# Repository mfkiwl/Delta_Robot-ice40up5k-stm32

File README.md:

[//]: # (Programado con lenguaje Markdown)

# DELTA ROBOT

Diseño robot delta

## Introducción

## Requerimientos

## Diseño

Se creo un [foro](https://xmartplm.com/covid19-colombia/) para la discusión en comunidad sobre el diseño de un ventilador para afrontar la crisis del COVID-19. Como conclusión se deben afrontar los siguientes temas:

* Seleccionar tipo de control.
* Diseño mecánico.
* Diseño electrónico.
* Realización prototipo.
* Pruebas.

### Diseño electrónico general

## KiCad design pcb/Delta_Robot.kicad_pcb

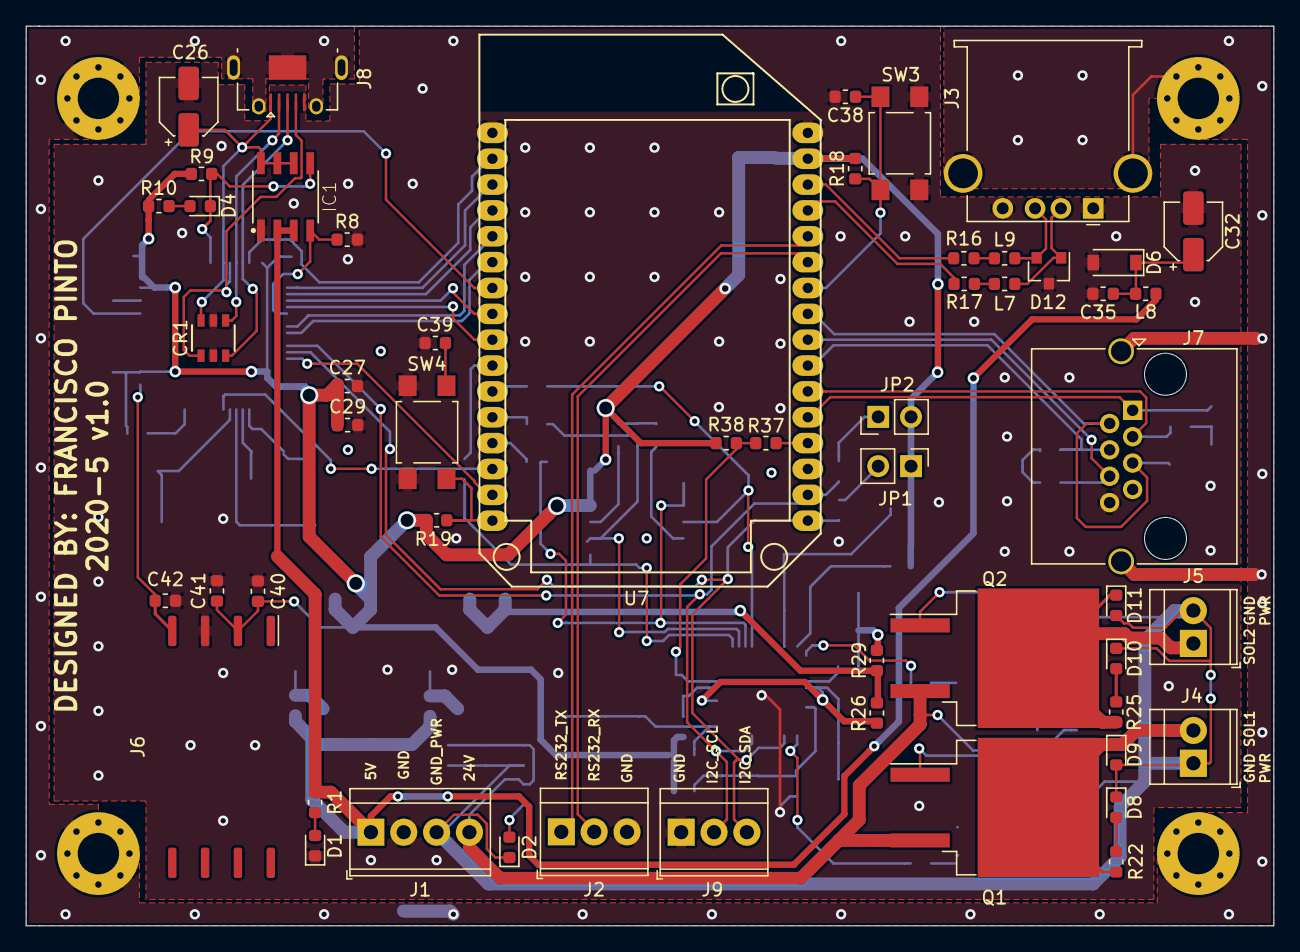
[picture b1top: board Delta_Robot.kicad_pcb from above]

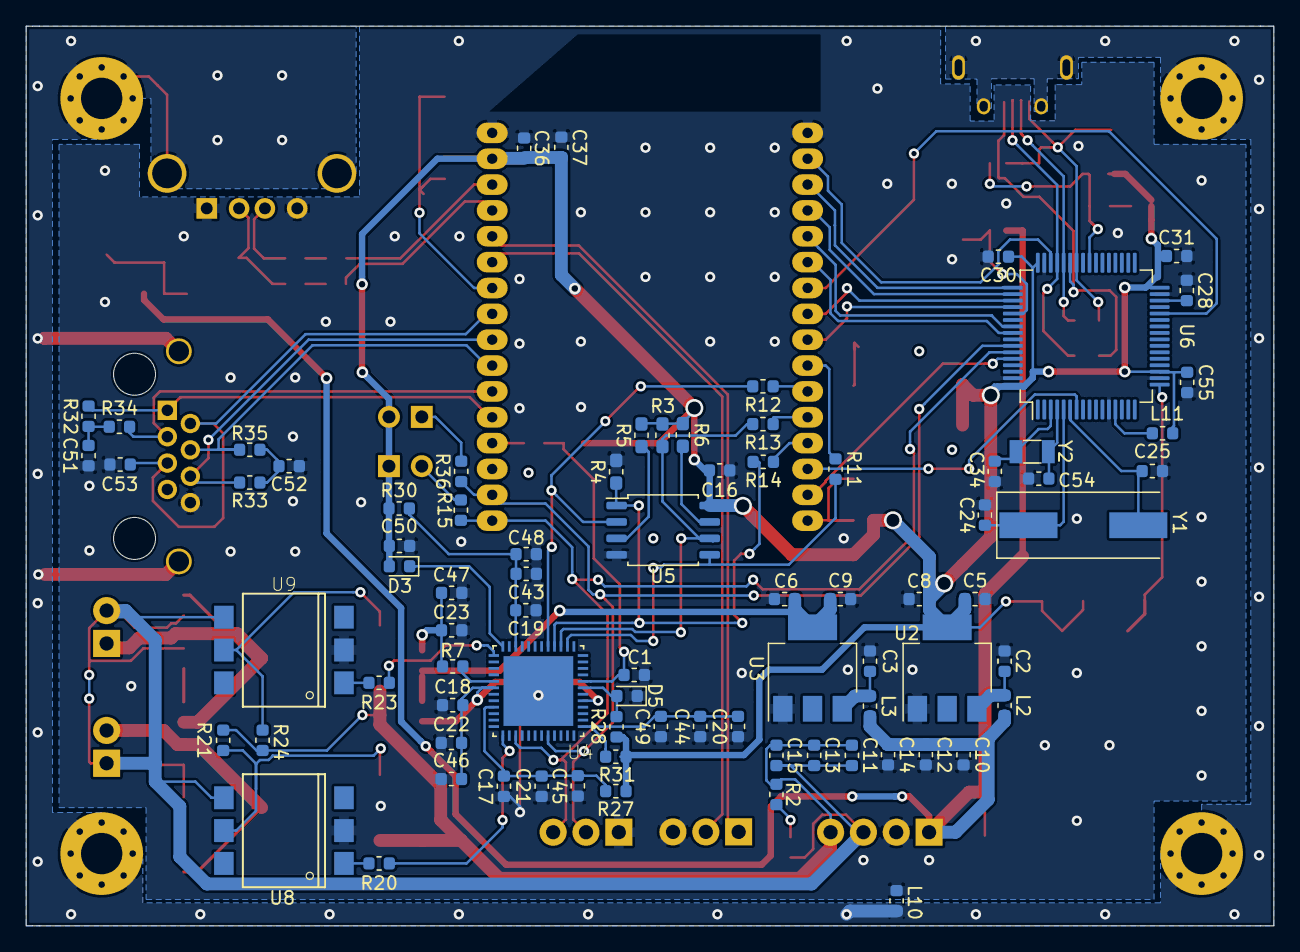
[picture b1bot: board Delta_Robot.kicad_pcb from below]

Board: 2 copper layers, 96.5 x 69.6 mm, 139 parts (81 on the bottom side), 87 nets.

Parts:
C1, C5, C6, C12, C13, C16, C21, C22, C27, C29, C30, C31, C36, C37, C43, C44, C50, C55: 0.1uF; C_0603_1608Metric
C2, C17, C18, C19, C20, C40, C53: 1uF; C_0603_1608Metric
C3, C9: 33uF; C_0603_1608Metric
C8: 4.7uF; C_0603_1608Metric
C10, C11: 220uF; C_0603_1608Metric
C14, C15: 1nF; C_0603_1608Metric
C23: 10uF; C_0603_1608Metric
C24, C25: 4.3pF; C_0603_1608Metric
C26: 4.7uF; CP_Elec_4x3
C28: 2.2uF; C_0603_1608Metric
C32: 22uF; CP_Elec_4x3
C34, C54: 2pF; C_0603_1608Metric
C35, C38, C39: 0.1u; C_0603_1608Metric
C41, C45, C46, C48, C49: 10nF; C_0603_1608Metric
C42: 470pF; C_0603_1608Metric
C47, C51, C52: 100nF; C_0603_1608Metric
CR1: ESDA6V1BC6
D1, D2, D4, D5, D8, D10: LED; LED_0603_1608Metric
D3, D9, D11: CDBU0520; D_0603_1608Metric
D6: 1N4733AW; D_SOD-123
D12: NUP2105L; SOT-23
H1, H2, H3, H4: MountingHole_Pad; MountingHole_3.2mm_M3_Pad_Via
IC1: STMPS2151MTR; SOIC127P600X175-8N
J1: Conn_01x04; TerminalBlock_TE_282834-4_1x04_P2.54mm_Horizontal
J2, J9: Conn_01x03; TerminalBlock_TE_282834-3_1x03_P2.54mm_Horizontal
J3: USB_A; USB_A_Stewart_SS-52100-001_Horizontal
J4, J5: Conn_01x02; TerminalBlock_TE_282834-2_1x02_P2.54mm_Horizontal
J6: MP3V5050VC6U
J7: RJ45; RJ45_Amphenol_RJHSE5380
J8: USB_OTG; USB_Micro-AB_Molex_47590-0001
JP1, JP2: Jumper; PinHeader_1x02_P2.54mm_Vertical
L2, L3: BLM18SG121TN1D; L_0603_1608Metric
L7, L9, L11: SRF2012-900YA; L_0603_1608Metric
L8, L10: 742792651; L_0603_1608Metric
Q1, Q2: IRF9540STRLPBF; TO-263-2
R1: 2k; R_0603_1608Metric
R2: 4k7; R_0603_1608Metric
R3, R5, R6: 10k; R_0603_1608Metric_Pad1.05x0.95mm_HandSolder
R4: 10K; R_0603_1608Metric_Pad1.05x0.95mm_HandSolder
R7, R11, R12, R13, R14, R37: 100; R_0603_1608Metric
R8, R9, R18, R19, R38: 10k; R_0603_1608Metric
R10: 620; R_0603_1608Metric
R15, R36: 4.7k; R_0603_1608Metric
R16, R17: 0K; R_0603_1608Metric
R20, R23: 330; R_0603_1608Metric
R21, R24: 100k; R_0603_1608Metric
R22, R25: 1k; R_0603_1608Metric
R26, R27, R29, R30, R31: 1; R_0603_1608Metric
R28: 2.2k; R_0603_1608Metric
R32, R33, R34, R35: 50; R_0603_1608Metric
SW3, SW4: TL3305A; SW_SPST_TL3305A
U2: LDL1117S33R; SOT-223-3_TabPin2
U3: ZLDO1117G12TA; SOT-223-3_TabPin2
U4: ICE40UP5K-SG48I; QFN50P700X700X100-49N
U5: W25Q64JVSSIQ; SOIC-8_5.23x5.23mm_P1.27mm
U6: STM32F412RGT6; LQFP-64_10x10mm_P0.5mm
U7: Omega2+; ONION_OMEGA2
U8, U9: 4N25-X007T; DIL6-SMD
Y1: 8MHz; Crystal_SMD_HC49-SD
Y2: 32.768KHZ; Crystal_SMD_3215-2Pin_3.2x1.5mm

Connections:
+1V2_FPGA: C6.1, C9.1, R26.2, R29.2, U3.2
+3V3: C5.1, C8.1, C16.1, C27.1, C29.1, C30.1, C31.1, C36.1, C37.1, C40.1, C41.1, C50.1, C55.1, D3.2, J6.2, JP1.1, JP2.2, L11.1, R3.1, R5.1, R6.1, R9.2, R10.2, R18.1, R19.1, R27.2, R28.2, R30.2, R31.2, R38.1, U2.2, U5.8, U6.19, U6.32, U6.48, U6.64, U7.31
+5V: C10.1, C12.1, C14.1, IC1.2, IC1.3, J1.1, L2.2, L3.2, L8.1, R1.1
+24V: C11.2, C13.2, C15.2, J1.4, Q1.3, Q2.3, R2.1, R21.1, R24.1
/External Communications/EXT_I2C0: J9.2, R36.2, U4.44, U6.58, U7.18
/External Communications/EXT_I2C1: J9.3, R15.2, U4.39, U6.59, U7.17
/External Communications/EXT_RS232_RX: J2.2, U7.27
/External Communications/EXT_RS232_TX: J2.1, U7.28
/FPGA/FPGA_CDONE: D5.2, R28.1, U4.7
/FPGA/FPGA_SOLENOID1: R20.2, U4.37
/FPGA/FPGA_SOLENOID2: R23.2, U4.25
/FPGA/FPGA_SPI0: R11.2, U4.14, U5.5
/FPGA/FPGA_SPI1: R12.2, U4.17, U5.2
/FPGA/FPGA_SPI2: R3.2, R13.2, U4.15, U5.6
/FPGA/FPGA_SPI3: R4.1, R14.2, U4.16, U5.1
/FPGA/FPGA_SPI_VCCIO_1: C19.2, C43.2, C48.2, R30.1, U4.22
/FPGA/FPGA_VCC: C18.2, C22.2, C46.2, R26.1, U4.5, U4.30
/FPGA/FPGA_VCCIO_2: C20.2, C44.2, C49.2, R31.1, U4.1
/FPGA/FPGA_VCCIO_O: C17.2, C21.2, C45.2, R27.1, U4.33
/FPGA/FPGA_VCCPLL: R7.1, U4.29
/FPGA/FPGA_VPP_2V5: D3.1, U4.24
/FPGA/~FPGA_CRESET_B: C1.2, R37.2, R38.2, U4.8
/FPGA/~FPGA_RESET: R37.1, U7.20
/Onion Omega 2/ETH_PWR: C53.1, J7.2, J7.5, U7.25
/Onion Omega 2/OMEGA2_ETH_RX+: J7.1, R32.2, U7.21
/Onion Omega 2/OMEGA2_ETH_RX-: J7.3, R34.2, U7.22
/Onion Omega 2/OMEGA2_ETH_TX+: J7.4, R35.1, U7.23
/Onion Omega 2/OMEGA2_ETH_TX-: J7.6, R33.1, U7.24
/Onion Omega 2/OMEGA2_FW_RST: C38.1, R18.2, SW3.2, U7.26
/Onion Omega 2/OMEGA2_JTAG_TCK: U6.49, U7.3
/Onion Omega 2/OMEGA2_JTAG_TDI: U6.50, U7.4
/Onion Omega 2/OMEGA2_JTAG_TDO: U6.55, U7.5
/Onion Omega 2/OMEGA2_JTAG_TMS: U6.46, U7.2
/Onion Omega 2/OMEGA2_JTAG_TRST: U6.56, U7.6
/Onion Omega 2/OMEGA2_USB_D+: R16.1, U7.30
/Onion Omega 2/OMEGA2_USB_D-: R17.2, U7.29
/Onion Omega 2/Omega2_SER1_RX: U6.51, U7.8
/Onion Omega 2/Omega2_SER1_TX: U6.52, U7.9
/Onion Omega 2/STM32_BOOT0: U6.60, U7.15
/Onion Omega 2/STM32_BOOT1: U6.28, U7.7
/Onion Omega 2/STM32_NRST: U6.7, U7.14
/Onion Omega 2/~OMEGA2_RST: C39.1, R19.2, SW4.2, U7.16
/STM32/PRESSURE_AIN: C42.1, J6.4, U6.17
/STM32/STM32_USB_DM: CR1.4, J8.2, U6.44
/STM32/STM32_USB_DP: CR1.3, J8.3, U6.45
/STM32/STM32_USB_ID: CR1.1, J8.4, U6.43
/STM32/STM32_USB_OverCurrent: D4.1, IC1.5, R9.1, U6.40
/STM32/STM32_USB_PowerSwitchOn: IC1.4, R8.2, U6.53
/STM32/STM32_USB_VBUS: C26.1, CR1.6, IC1.6, IC1.7, IC1.8, J8.1, U6.42
GND: C1.1, C2.2, C3.2, C5.2, C6.2, C8.2, C9.2, C10.2, C12.2, C14.2, C16.2, C17.1, C18.1, C19.1, C20.1, C21.1, C22.1, C23.1, C24.2, C25.2, C26.2, C27.2, C28.2, C29.2, C30.2, C31.2, C32.2, C34.2, C35.2, C36.2, C37.2, C38.2, C39.2, C40.2, C41.2, C42.2, C43.1, C44.1, C45.1, C46.1, C47.1, C48.1, C49.1, C50.2, C51.1, C52.2, C53.2, C54.2, C55.2, CR1.2, CR1.5, D1.1, D5.1, D6.2, D12.3, IC1.1, J1.2, J2.3, J3.1, J3.4, J6.3, J7.8, J8.5, J9.1, L10.2, R4.2, R8.1, SW3.1, SW4.1, U2.1, U3.1, U4.EP, U5.4, U6.12, U6.18, U6.31, U6.47, U6.63, U7.1, U7.32, U8.2, U9.2
GNDPWR: C11.1, C13.1, C15.1, D2.1, D8.1, D9.2, D10.1, D11.2, J1.3, J4.1, J5.2, U8.4, U9.4
GND_CASE: H1.1, H2.1, H3.1, H4.1, J3.5, J7.SH, J8.6, L10.1
unnamed: C2.1, L2.1, U2.3
unnamed: C3.1, L3.1, U3.3
unnamed: C23.2, C47.2, R7.2, R29.1
unnamed: C24.1, U6.5, Y1.1
unnamed: C25.1, U6.6, Y1.2
unnamed: C28.1, U6.30
unnamed: C32.1, C35.1, D6.1, L8.2
unnamed: C34.1, U6.3, Y2.1
unnamed: C51.2, R32.1, R34.1
unnamed: C52.1, R33.2, R35.2
unnamed: C54.1, U6.4, Y2.2
unnamed: D1.2, R1.2
unnamed: D2.2, R2.2
unnamed: D4.2, R10.1
unnamed: D8.2, R22.2
unnamed: D9.1, J4.2, Q1.2, R22.1
unnamed: D10.2, R25.2
unnamed: D11.1, J5.1, Q2.2, R25.1
unnamed: D12.1, J3.2, L7.2
unnamed: D12.2, J3.3, L9.2
unnamed: JP1.2, R15.1
unnamed: JP2.1, R36.1
unnamed: L7.1, R17.1
unnamed: L9.1, R16.2
unnamed: L11.2, U6.13
unnamed: Q1.1, R21.2, U8.5
unnamed: Q2.1, R24.2, U9.5
unnamed: R5.2, U5.3
unnamed: R6.2, U5.7
unnamed: R11.1, U7.10
unnamed: R12.1, U7.11
unnamed: R13.1, U7.12
unnamed: R14.1, U7.13
unnamed: R20.1, U8.1
unnamed: R23.1, U9.1

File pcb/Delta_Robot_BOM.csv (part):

Reference, Quantity, Value, Footprint, Datasheet, Digikey, MPN, Mouser, Breakout board, Field4, Field5, Field6, Value2, Description, Manufacturer_Name, Drawing
C10 C3 C9 ,3,"22uF","Capacitor_SMD:C_0603_1608Metric","~","1276-2868-1-ND","CL10A226MQ8NRNE","","","","","","","","",""
C11 C23 ,2,"10uF","Capacitor_SMD:C_0603_1608Metric","~","1253-CM105X5R106M25ATCT-ND","CM105X5R106M25AT","346-CM105X5R106M25AT","","","","","","","",""
C12 C13 C5 C6 C16 C22 C47 C50 C21 C43 C44 C1 C55 C29 C30 C31 C27 C36 C35 C38 C39 C52 C37 ,23,"0.1uF","Capacitor_SMD:C_0603_1608Metric","~","399-7845-1-ND","C0603C104M5RACTU","80-C0603C104M5R","","","","","","","",""
C14 C15 ,2,"1nF","Capacitor_SMD:C_0603_1608Metric","~","311-1080-1-ND","CC0603KRX7R9BB102","603-CC603KRX7R9BB102","","","","","","","",""
C2 C18 C17 C19 C20 C53 C40 ,7,"1uF","Capacitor_SMD:C_0603_1608Metric","~","1276-1102-1-ND","CL10A105KA8NNNC","","","","","","","","",""
C25 C24 ,2,"4.3pF","Capacitor_SMD:C_0603_1608Metric","~","1276-2309-1-ND","CL10C4R3CB8NNNC","","","","","","","","",""
C26 ,1,"4.7uF","Capacitor_SMD:CP_Elec_4x3","https://www.we-online.de/katalog/datasheet/865060240001.pdf","732-8569-1-ND","865060240001","710-865060240001","","","","","","","",""
C28 ,1,"2.2uF","Capacitor_SMD:C_0603_1608Metric","~","587-1430-1-ND","EMK107BJ225KA-T","963-EMK107BJ225KA-T","","","","","","","",""
C32 ,1,"22uF","Capacitor_SMD:CP_Elec_4x3","https://www.we-online.de/katalog/datasheet/865060240001.pdf","732-8569-1-ND","865060240001","710-865060240001","","","","","","","",""
C42 ,1,"470pF","Capacitor_SMD:C_0603_1608Metric","~","399-1075-1-ND","C0603C471K5RACTU","80-C0603C471K5R","","","","","","","",""
C46 C45 C48 C49 C41 ,5,"10nF","Capacitor_SMD:C_0603_1608Metric","~","399-7842-1-ND","C0603C103M5RACTU","80-C0603C103M5R","","","","","","","",""
C51 ,1,"100nF","Capacitor_SMD:C_0603_1608Metric","~","399-1100-1-ND","C0603C104Z3VACTU","80-C0603C104Z3V","","","","","","","",""
C54 C34 ,2,"2pF","Capacitor_SMD:C_0603_1608Metric","~","1276-2124-1-ND","CL10C020CB8NNNC","","","","","","","","",""
C8 ,1,"4.7uF","Capacitor_SMD:C_0603_1608Metric","~","1276-1907-1-ND","CL10A475MQ8NNNC","","","","","","","","",""
CR1 ,1,"ESDA6V1BC6","SMD:ESDA6V1BC6","https://www.st.com/content/ccc/resource/technical/document/d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","497-6635-1-ND","ESDA6V1BC6","511-ESDA6V1BC6","","","","","","","",""
D1 D2 D5 D4 D8 D10 ,6,"LED","LED_SMD:LED_0603_1608Metric","~","732-4971-1-ND","150060GS75000","710-150060GS75000","","","","","","","",""
D12 ,1,"NUP2105L","Package_TO_SOT_SMD:SOT-23","http://www.onsemi.com/pub_link/Collateral/NUP2105L-D.PDF","SZNUP2105LT1GOSCT-ND","SZNUP2105LT1G","863-SZNUP2105LT1G","","","","","","","",""
D3 D9 D11 ,3,"CDBU0520","Diode_SMD:D_0603_1608Metric","http://www.comchiptech.com/admin/files/product/CDBU0520-HF-R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","641-1332-1-ND","CDBU0520","750-CDBU0520","","","","","","","",""
D6 ,1,"BZT52-B5V1J","Diode_SMD:D_SOD-123","~","1727-7742-1-ND","BZT52-B5V1J","771-BZT52-B5V1J","","","","","","","",""
H1 H2 H3 H4 ,4,"MountingHole_Pad","MountingHole:MountingHole_3.2mm_M3_Pad_Via","~"
IC1 ,1,"STMPS2151MTR","SMD:SOIC127P600X175-8N","http://docs-emea.rs-online.com/webdocs/140d/0900766b8140da90.pdf","497-8349-1-ND","STMPS2151MTR","511-STMPS2151MTR","","","","","","STMICROELECTRONICS - STMPS2151MTR","STMicroelectronics",""
J1 ,1,"Conn_01x04","TerminalBlock_TE-Connectivity:TerminalBlock_TE_282834-4_1x04_P2.54mm_Horizontal","~","A98335-ND","282834-4","571-282834-4","","","","","","","",""
J2 J9 ,2,"Conn_01x03","TerminalBlock_TE-Connectivity:TerminalBlock_TE_282834-3_1x03_P2.54mm_Horizontal","~","A98334-ND","282834-3","571-2828343","","","","","","","",""
J3 ,1,"USB_A","Connector_USB:USB_A_Stewart_SS-52100-001_Horizontal","https://belfuse.com/resources/datasheets/stewartconnector/ds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","380-1412-ND","SS-52100-001","530-SS-52100-001","","","","","","","",""
J4 J5 ,2,"Conn_01x02","TerminalBlock_TE-Connectivity:TerminalBlock_TE_282834-2_1x02_P2.54mm_Horizontal","~","A98333-ND","282834-2","571-282834-2","","","","","","","",""
J6 ,1,"MP3V5050VC6U","SMD:MP3V5050VC6U","https://www.nxp.com/docs/en/data-sheet/MP3V5050V.pdf","568-MP3V5050VC6U-ND","MP3V5050VC6U","841-MP3V5050VC6U","","","","","","","",""
J7 ,1,"RJ45","Connector_RJ:RJ45_Amphenol_RJHSE5380","https://cdn.amphenol-icc.com/media/wysiwyg/files/drawing/rjh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","RJHSE-5380-ND","RJHSE-5380","523-RJHSE-5380","","","","","","","",""
J8 ,1,"USB_OTG","SMD:USB_Micro-AB_Molex_47590-0001","https://www.molex.com/pdm_docs/sd/475900001_sd.pdf","WM17144CT-ND","0475900001","538-47590-0001","","","","","","","",""
JP2 JP1 ,2,"Jumper","Connector_PinHeader_2.54mm:PinHeader_1x02_P2.54mm_Vertical","~"
L10 L8 ,2,"742792651","Inductor_SMD:L_0603_1608Metric","https://www.we-online.de/katalog/datasheet/742792651.pdf","732-1593-1-ND","742792651","710-742792651","","","","","","","",""
L11 L9 L7 ,3,"SRF2012-900YA","Inductor_SMD:L_0603_1608Metric","https://www.bourns.com/docs/Product-Datasheets/SRF2012A.pdf","SRF2012-900YACT-ND","SRF2012-900YA","652-SRF2012-900YA","","","","","","","",""
L2 L3 ,2,"BLM18SG121TN1D","Inductor_SMD:L_0603_1608Metric","~","490-3996-6-ND","BLM18SG121TN1D","81-BLM18SG121TN1D","","","","","","","",""
Q1 Q2 ,2,"IRF9540STRLPBF","Package_TO_SOT_SMD:TO-263-2","http://www.vishay.com/docs/91079/91079.pdf","IRF9540STRLPBFCT-ND","IRF9540STRLPBF","844-IRF9540STRLPBF","","","","","","","",""
R1 R7 R37 R11 R12 R13 R14 ,7,"100","Resistor_SMD:R_0603_1608Metric","~","311-100HRCT-ND","RC0603FR-07100RL","603-RC0603FR-07100RL","","","","","","","",""
R15 R36 ,2,"4.7k","Resistor_SMD:R_0603_1608Metric","~","RR08P4.7KDCT-ND","RR0816P-472-D","","","","","","","","",""
R17 R16 ,2,"0K","Resistor_SMD:R_0603_1608Metric","~","311-0.0GRCT-ND","RC0603JR-070RL","603-RC0603JR-070RL","","","","","","","",""
R2 R22 R25 ,3,"1.5k","Resistor_SMD:R_0603_1608Metric","~","A130092CT-ND","CRGCQ0603J1K5","279-CRGCQ0603J1K5","","","","","","","",""
R20 R23 ,2,"47","Resistor_SMD:R_0603_1608Metric","~","A130083CT-ND","CRGCQ0603J47R","279-CRGCQ0603J47R","","","","","","","",""
R21 R24 ,2,"100k","Resistor_SMD:R_0603_1608Metric","~","RR08P100KDCT-ND","RR0816P-104-D","754-RR0816P-104D","","","","","","","",""
R26 R29 R27 R30 R31 ,5,"1","Resistor_SMD:R_0603_1608Metric","~","311-1.00HRCT-ND","RC0603FR-071RL","603-RC0603FR-071RL","","","","","","","",""
R28 R10 ,2,"4.7","Resistor_SMD:R_0603_1608Metric","~","2019-RK73B1JTTD4R7JCT-ND","RK73B1JTTD4R7J","660-RK73B1JTTD4R7J","","","","","","","",""
R32 R34 R35 R33 ,4,"50","Resistor_SMD:R_0603_1608Metric","~","A130083CT-ND","CRGCQ0603J47R","279-CRGCQ0603J47R","","","","","","","",""
R38 R8 R9 R18 R19 ,5,"10k","Resistor_SMD:R_0603_1608Metric","~","311-10KGRCT-ND","RC0603JR-0710KL","603-RC0603JR-0710KL","","","","","","","",""
R4 R5 R6 R3 ,4,"10k","Resistor_SMD:R_0603_1608Metric_Pad1.05x0.95mm_HandSolder","~","311-10KGRCT-ND","RC0603JR-0710KL","603-RC0603JR-0710KL","","","","","","","",""
SW3 SW4 ,2,"TL3305A","Button_Switch_SMD:SW_SPST_TL3305A","https://sten-eswitch-13110800-production.s3.amazonaws.com/sy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","EG5353CT-ND","TL3305AF260QG","612-TL3305AF260QG","","","","","","","","http://spec_sheets.e-switch.com/specs/P010471.pdf"
U2 ,1,"LDL1117S33R","Package_TO_SOT_SMD:SOT-223-3_TabPin2","https://www.st.com/content/ccc/resource/technical/document/d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","497-17239-1-ND","LDL1117S33R","511-LDL1117S33R","","","","","","","",""
U3 ,1,"ZLDO1117G12TA","Package_TO_SOT_SMD:SOT-223-3_TabPin2","https://www.diodes.com/assets/Datasheets/ZLDO1117.pdf","ZLDO1117G12DICT-ND","ZLDO1117G12TA","522-ZLDO1117G12TA","","","","","","","",""
U4 ,1,"ICE40UP5K-SG48I","SMD:QFN50P700X700X100-49N","http://www.latticesemi.com/view_document?document_id=51968","220-2212-1-ND","ICE40UP5K-SG48I","842-ICE40UP5K-SG48I","https://www.mouser.com/datasheet/2/225/FPGAUG0200110-1324499.pdf","1.4","Lattice Semiconductor","10381","","","",""
U5 ,1,"W25Q64JVSSIQ","Package_SO:SOIC-8_5.23x5.23mm_P1.27mm","https://www.winbond.com/resource-files/w25q64jv%20revj%20032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","W25Q64JVSSIQ-ND","W25Q64JVSSIQ","454-W25Q64JVSSIQ","","","","","","","",""
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
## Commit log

2020-04-15 Creacion repositorio
2020-04-15 Modificacion a delta robot
2020-04-16 KiCAD inicio PCB
2020-04-16 Modificacion senales bidireccionales
2020-04-21 Adicion STM32
2020-04-23 Modificacion STM32
2020-04-23 Modificacion USART STM32
2020-04-28 Cambio sensor presion
2020-04-30 Adicion footprints
2020-04-30 Generacion annotate
2020-05-04 Cambio simbolo FPGA
2020-05-04 Adicion enlace FPGA breakout board
2020-05-04 Eliminacion librerias UNAL
2020-05-04 Add files via upload
    Adicion librerias
2020-05-04 Add files via upload
    Adicion libreria
2020-05-12 Organizacion basica PCB
2020-05-19 Modificacion general PCB
2020-05-21 Adicion zona GND
2020-05-21 Mejora footprint USB-A-B
2020-05-22 Correccion UART Micro-Omega2
2020-05-22 Generacion gerbers
2020-05-29 PCB finalizado (Enviado a fabricacion)
2020-05-29 BOM finished
2020-06-08 Shopping list OK
2020-06-16 CAD Carcasa
2020-06-16 Carcasa modificacion
